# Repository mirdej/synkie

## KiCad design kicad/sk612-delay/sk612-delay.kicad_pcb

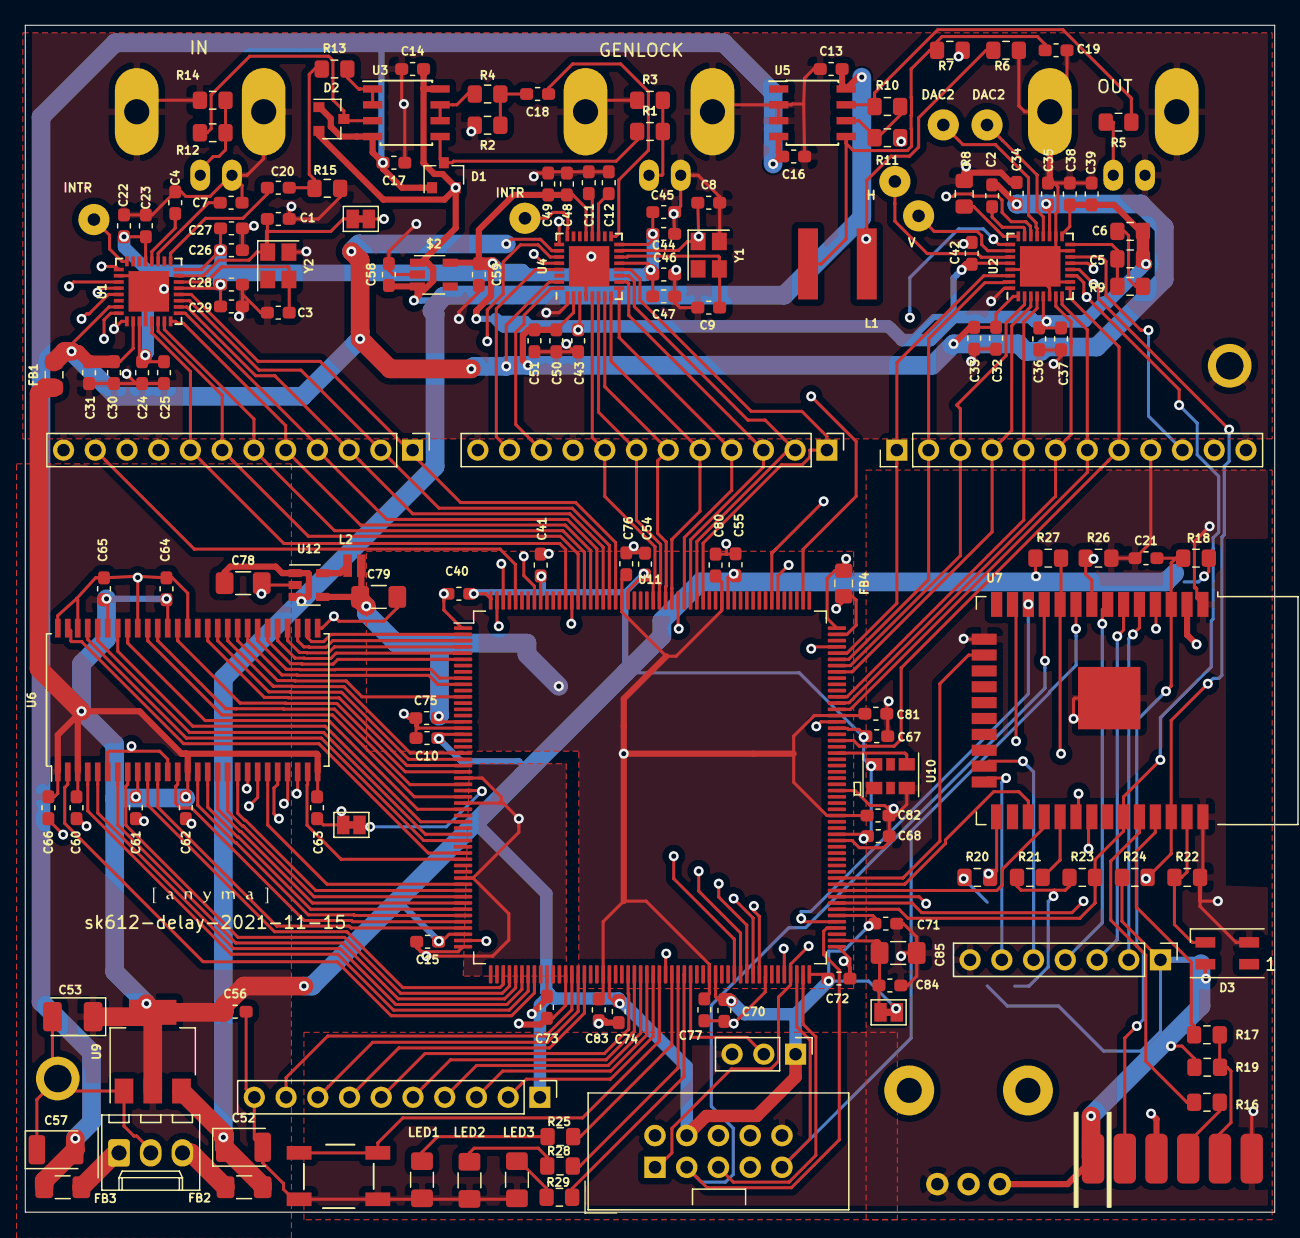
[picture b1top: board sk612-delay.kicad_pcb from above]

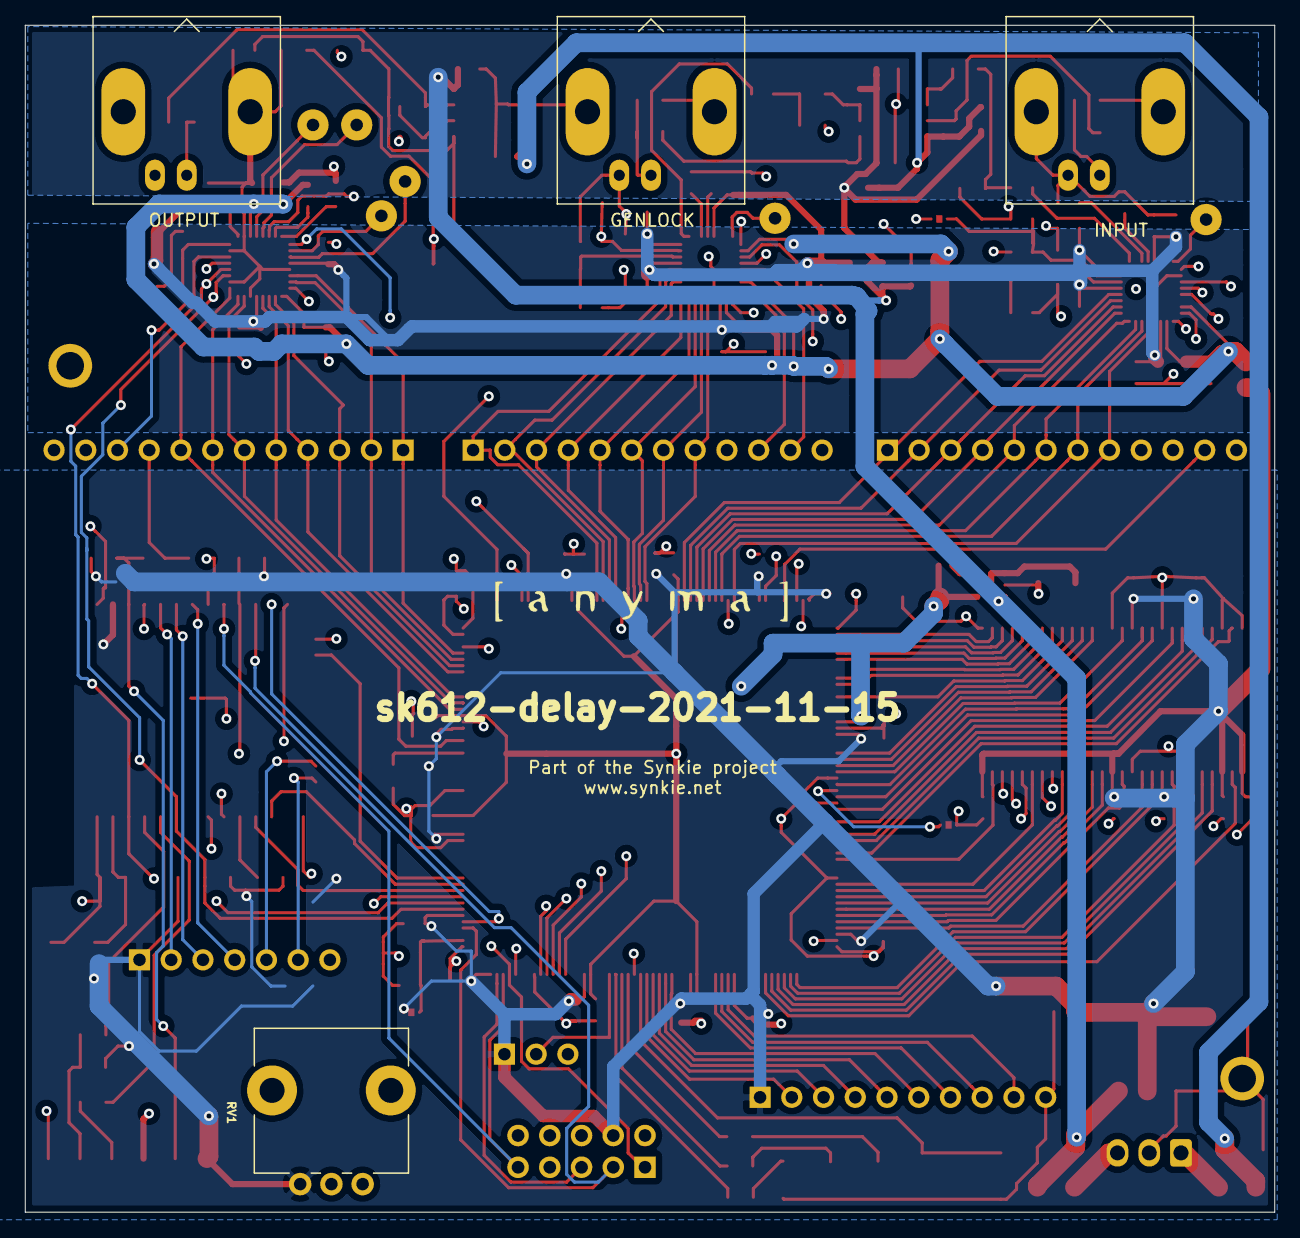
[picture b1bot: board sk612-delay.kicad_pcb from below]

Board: 4 copper layers, 100.0 x 95.0 mm, 166 parts (5 on the bottom side), 159 nets.

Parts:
$2: ADP150; TSOT-23-5
C1, C3, C8, C9: 18p; C_0603_1608Metric_Pad1.05x0.95mm_HandSolder
C2: 2n2; C_0603_1608Metric_Pad1.05x0.95mm_HandSolder
C4, C7, C10, C11, C12, C13, C14, C15, C16, C17, C18, C20, C23, C25, C27, C29, C31, C33, C35, C37, C39, C40, C41, C43, C45, C47, C49, C51, C54, C55, C56, C60, C61, C62, C63, C64, C65, C66, C67, C68, C70, C71, C72, C73, C74, C75, C76, C77, C80, C81, C82, C83, C84: 100n; C_0603_1608Metric_Pad1.05x0.95mm_HandSolder
C5: 12n; C_0805_2012Metric_Pad1.15x1.40mm_HandSolder
C6: 150n; C_0805_2012Metric_Pad1.15x1.40mm_HandSolder
C19: 22p; C_0603_1608Metric_Pad1.05x0.95mm_HandSolder
C21, C58, C59: 1u; C_0603_1608Metric_Pad1.05x0.95mm_HandSolder
C22, C24, C26, C28, C30, C32, C34, C36, C38, C42, C44, C46, C48, C50: 10n; C_0603_1608Metric_Pad1.05x0.95mm_HandSolder
C52, C57: 10u; CP_EIA-3528-21_Kemet-B
C53: 10u; CP_EIA-3528-21_Kemet-B_Pad1.50x2.35mm_HandSolder
C78: 10u; C_1206_3216Metric_Pad1.42x1.75mm_HandSolder
C79: 22u; C_1206_3216Metric_Pad1.42x1.75mm_HandSolder
C85: 33u; C_1206_3216Metric_Pad1.42x1.75mm_HandSolder
D1, D2: BAT54S; SOT-23
D3: SK6812MINI; LED_SK6812MINI_PLCC4_3.5x3.5mm_P1.75mm
D4, D5, D6: LED; C_1206_3216Metric_Pad1.42x1.75mm_HandSolder
FB1, FB4: Ferrite_Bead; L_0805_2012Metric_Pad1.15x1.40mm_HandSolder
FB2, FB3: Ferrite_Bead; L_1206_3216Metric_Pad1.42x1.75mm_HandSolder
H1, H2: MountingHole_Pad; MountingHole_2.2mm_M2_ISO7380_Pad
J1, J23: intr; Solderpad_1mm
J2, J5, J10: Conn_01x12; PinHeader_1x12_P2.54mm_Vertical
J3: vs; Solderpad_1mm
J4: hs; Solderpad_1mm
J6: dac2; Solderpad_1mm
J7: dac3; Solderpad_1mm
J8: Genlock IN; BNC_MOLEX_0731000080_Horizontal
J9: OUT; BNC_MOLEX_0731000080_Horizontal
J11: Conn_01x07; PinHeader_1x07_P2.54mm_Vertical
J12: Conn_01x10; IDC-Header_2x05_P2.54mm_Vertical
J13: Mode-Switch; PinHeader_1x03_P2.54mm_Vertical
J14: Conn_01x10; PinHeader_1x10_P2.54mm_Vertical
J15: Video In; BNC_MOLEX_0731000080_Horizontal
J17: Conn_01x06; Pinhead_SMD_6
J19: Supply; Molex_KK-254_AE-6410-03A_1x03_P2.54mm_Vertical
JP1: Jumper_2_Bridged; SolderJumper-2_P1.3mm_Bridged_Pad1.0x1.5mm
JP2, JP3: Jumper; SolderJumper-2_P1.3mm_Bridged_Pad1.0x1.5mm
L1: 10uH; Murata 1264EY-Inductor
L2: L; L-WUERTH-WE_MAIA
R1, R3, R5, R12, R14: 75; R_0805_2012Metric_Pad1.15x1.40mm_HandSolder
R2, R13: 24; R_0805_2012Metric_Pad1.15x1.40mm_HandSolder
R4, R15: 51; R_0805_2012Metric_Pad1.15x1.40mm_HandSolder
R6, R7: 600; R_0805_2012Metric_Pad1.15x1.40mm_HandSolder
R8: 4k12; R_0805_2012Metric_Pad1.15x1.40mm_HandSolder
R9: 170; R_0805_2012Metric_Pad1.15x1.40mm_HandSolder
R10, R11: 560; R_0805_2012Metric_Pad1.15x1.40mm_HandSolder
R16, R17: 330; R_0805_2012Metric_Pad1.15x1.40mm_HandSolder
R18, R19, R20, R21, R22, R27: 10k; R_0805_2012Metric_Pad1.15x1.40mm_HandSolder
R23, R24: 4k7; R_0805_2012Metric_Pad1.15x1.40mm_HandSolder
R25, R26, R28, R29: 1k; R_0805_2012Metric_Pad1.15x1.40mm_HandSolder
RV1: delay-time; Potentiometer_Alps_RK09L_Single_Vertical
SW1: SW_Push; Alps_Tactile_Switch
U1, U4: ADV7280; LFCSP-32-1EP_5x5mm_P0.5mm_EP3.25x3.25mm
U2: ADV7391; LFCSP-32-1EP_5x5mm_P0.5mm_EP3.25x3.25mm
U3, U5: LMH6643; SOIC-8_3.9x4.9mm_P1.27mm
U6: IS42_S16320F; TSOP-II-54_22.2x10.16mm_P0.8mm
U7: ESP32-WROOM; ESP32-WROOM-32
U8: LOGO; logo_anyma_tiny
U9: AZ1117-3.3; SOT-223-3_TabPin2
U10: OSC-RENESAS
U11: A3P125-PQG208; PQFP-208_28x28mm_P0.5mm
U12: VREG-SC189C; SOT-23-5
U13: LOGO; logo_anyma
Y1: Crystal_GND24; Crystal_SMD_Abracon_ABM8G-4Pin_3.2x2.5mm
Y2: Crystal??; Crystal_SMD_Abracon_ABM8G-4Pin_3.2x2.5mm

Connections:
3V3: C10.1, C15.1, C40.1, C41.1, C53.1, C54.1, C55.1, C56.1, C60.1, C61.1, C62.1, C63.1, C64.1, C65.1, C66.1, C67.1, C68.1, C70.1, C71.1, C72.1, C73.1, C74.1, D3.4, FB1.1, J11.1, J12.4, J13.1, J14.1, J17.1, JP2.2, R18.1, R19.1, R20.1, R21.1, R23.1, R24.1, R27.1, RV1.3, U6.1, U6.3, U6.9, U6.14, U6.27, U6.43, U6.49, U7.2, U9.2, U10.6, U11.18, U11.50, U11.62, U11.72, U11.89, U11.104, U11.110, U11.123, U11.140, U11.170, U11.186, U11.200, U11.208
200MHZ: U10.4, U11.136
+1V5: C75.1, C76.1, C77.1, C79.1, C80.1, C81.1, C82.1, C83.1, L2.1, U11.16, U11.71, U11.88, U11.126, U11.142, U11.171, U11.187, U12.4
+1V8: $2.5, C5.1, C6.1, C22.2, C23.2, C24.2, C25.2, C26.2, C27.2, C28.2, C29.2, C36.2, C37.2, C38.2, C39.2, C42.2, C43.2, C44.2, C45.2, C46.2, C47.2, C48.2, C49.2, C59.1, U1.3, U1.13, U1.16, U1.21, U2.5, U2.17, U2.28, U4.3, U4.13, U4.16, U4.21
+3V3: C2.1, C30.2, C31.2, C32.2, C33.2, C34.2, C35.2, C50.2, C51.2, FB1.2, U1.2, U1.31, U2.1, U2.19, U4.2, U4.26, U4.31
+5V: $2.1, $2.3, C13.2, C14.2, C52.1, C58.1, C78.1, D1.2, D2.2, FB2.1, U3.8, U5.8, U9.3, U12.1, U12.3
-5V: C16.2, C17.2, C57.2, D1.1, D2.1, FB3.1, U3.4, U5.4
/controller/cs: R21.2, U7.29
/controller/en: C21.1, J17.2, R18.2, U7.3
/controller/gpio0: J17.3, R20.2, U7.25
/controller/led: D3.3, R22.1, U7.37
/controller/rx: J17.4, R16.2
/controller/tx: J17.5, R17.2, R19.2
/fpga/btn: SW1.2, U11.80
/fpga/led1: R25.1, U11.82
/fpga/led2: R28.1, U11.83
/fpga/led3: R29.1, U11.84
/fpga/switch: J13.2, U11.85
A0: U6.23, U11.94
A1: U6.24, U11.93
A2: U6.25, U11.92
A3: U6.26, U11.38
A4: U6.29, U11.2
A5: U6.30, U11.3
A6: U6.31, U11.4
A7: U6.32, U11.5
A8: U6.33, U11.6
A9: U6.34, U11.9
A10: U6.22, U11.42
A11: U6.35, U11.10
A12: U6.36, U11.12
AD0: J10.1, U1.12, U11.188
AD1: J10.2, U1.11, U11.189
AD2: J10.3, U1.10, U11.190
AD3: J10.4, U1.9, U11.191
AD4: J10.5, U1.8, U11.192
AD5: J10.6, U1.7, U11.193
AD6: J10.7, U1.6, U11.194
AD7: J10.8, U1.5, U11.196
ADC_IN: C20.1, U1.17
ADC_LLC: J10.10, U1.32, U11.206
ADC_RESET: U1.25, U4.25, U7.31
AD_SFL_OUT: J10.11, U1.29, U11.204
BA0: U6.20, U11.95
BA1: U6.21, U11.96
CAS: U6.17, U11.45
CKE: U6.37, U11.21
CS: U6.19, U11.43
DA0: J2.1, U2.30, U11.152
DA1: J2.2, U2.31, U11.151
DA2: J2.3, U2.2, U11.150
DA3: J2.4, U2.3, U11.149
DA4: J2.5, U2.4, U11.145
DA5: J2.6, U2.7, U11.144
DA6: J2.7, U2.8, U11.143
DA7: J2.8, U2.9, U11.138
DAC_CLK: U2.13, U11.163
DAC_OUT: L1.2, R6.1, U2.22
DAC_RESET: J2.10, U2.14, U7.30
DAC_SFL_IN: U2.25, U11.153
DGMH: U6.39, U11.23
DQ0: U6.2, U11.60
DQ1: U6.4, U11.59
DQ2: U6.5, U11.58
DQ3: U6.7, U11.57
DQ4: U6.8, U11.56
DQ5: U6.10, U11.55
DQ6: U6.11, U11.49
DQ7: U6.13, U11.48
DQ8: U6.42, U11.24
DQ9: U6.44, U11.26
DQ10: U6.45, U11.28
DQ11: U6.47, U11.30
DQ12: U6.48, U11.32
DQ13: U6.50, U11.34
DQ14: U6.51, U11.35
DQ15: U6.53, U11.37
DQML: U6.15, U11.47
GENLOCK_ADC_IN: C18.1, U4.17
GL0: J5.1, U4.12, U11.174
GL1: J5.2, U4.11, U11.175
GL2: J5.3, U4.10, U11.176
GL3: J5.4, U4.9, U11.177
GL4: J5.5, U4.8, U11.179
GL5: J5.6, U4.7, U11.180
GL6: J5.7, U4.6, U11.181
GL7: J5.8, U4.5, U11.182
GL_LLC: J5.10, U4.32, U11.201
GL_SFL_OUT: J5.11, U4.29, U11.158
GND: $2.2, C1.2, C3.1, C4.1, C7.1, C8.2, C9.1, C10.2, C11.1, C12.1, C13.1, C14.1, C15.2, C16.1, C17.1, C19.2, C21.2, C22.1, C23.1, C24.1, C25.1, C26.1, C27.1, C28.1, C29.1, C30.1, C31.1, C32.1, C33.1, C34.1, C35.1, C36.1, C37.1, C38.1, C39.1, C40.2, C41.2, C42.1, C43.1, C44.1, C45.1, C46.1, C47.1, C48.1, C49.1, C50.1, C51.1, C52.2, C53.2, C54.2, C55.2, C56.2, C57.1, C58.2, C59.2, C60.2, C61.2, C62.2, C63.2, C64.2, C65.2, C66.2, C67.2, C68.2, C70.2, C71.2, C72.2, C73.2, C74.2, C75.2, C76.2, C77.2, C78.2, C79.2, C80.2, C81.2, C82.2, C83.2, C84.2, C85.2, D3.2, D4.1, D5.1, D6.1, FB4.1, H1.1, H2.1, J2.9, J2.12, J5.9, J5.12, J8.2, J9.2, J10.9, J10.12, J11.7, J12.2, J12.10, J13.3, J14.10, J15.2, J17.6, J19.2, JP3.1, R3.1, R4.1, R6.2, R7.2, R8.2, R11.2, R14.1, R15.1, R22.2, R26.2, RV1.1, SW1.1, U1.1, U1.4, U1.26, U1.33, U2.6, U2.10, U2.15, U2.18, U2.29, U2.32, U2.33, U4.1, U4.4, U4.33, U5.2, U5.3, U6.6, U6.12, U6.28, U6.41, U6.46, U6.52, U6.54, U7.1, U7.15, U7.38, U7.39, U9.1, U10.3, U11.1, U11.17, U11.25, U11.29, U11.41, U11.52, U11.65, U11.81, U11.97, U11.105, U11.122, U11.130, U11.141, U11.156, U11.162, U11.178, U11.195, U12.2, Y1.4, Y2.4
GNDS: FB4.2, U11.51, U11.100, U11.155, U11.207
MISO: U7.16, U11.116
MOSI: U7.28, U11.114
unnamed: C1.1, JP1.2, U1.15, Y2.1
unnamed: C2.2, U2.23
unnamed: C3.2, U1.14, Y2.3
unnamed: C4.2, U1.20
unnamed: C5.2, R9.2, U2.16
unnamed: C6.2, R9.1
unnamed: C7.2, U1.19
unnamed: C8.1, JP1.1, U4.15, Y1.1
unnamed: C9.2, U4.14, Y1.3
unnamed: C11.2, U4.20
unnamed: C12.2, U4.19
unnamed: C18.2, R2.1, R4.2
unnamed: C19.1, L1.1, R7.1, U5.5
unnamed: C20.2, R13.1, R15.2
unnamed: C84.1, C85.1, JP2.1, U11.106
unnamed: D1.3, R1.1, U3.5
unnamed: D2.3, R12.1, U3.3
unnamed: D4.2, R25.2
unnamed: D5.2, R28.2
unnamed: D6.2, R29.2
unnamed: FB2.2, J19.3
unnamed: FB3.2, J19.1
unnamed: J1.1, U4.24
unnamed: J3.1, U2.26
unnamed: J4.1, U2.27
unnamed: J6.1, U2.21
unnamed: J7.1, U2.20
unnamed: J8.1, R1.2, R3.2
unnamed: J9.1, R5.2
unnamed: J11.2, U7.5
unnamed: J11.3, U7.6
unnamed: J11.4, U7.7
unnamed: J11.5, U7.23
unnamed: J11.6, U7.24
unnamed: J14.2, U11.79
unnamed: J14.3, U11.78
unnamed: J14.4, U11.77
unnamed: J14.5, U11.76
unnamed: J14.6, U11.75
unnamed: J14.7, U11.68
unnamed: J14.8, U11.67
unnamed: J14.9, U11.66
unnamed: J15.1, R12.2, R14.2
unnamed: J23.1, U1.24
unnamed: JP3.2, U11.27
unnamed: L2.2, U12.5
unnamed: R2.2, U3.6, U3.7
unnamed: R8.1, U2.24
unnamed: R10.1, R11.1, U5.6
unnamed: R5.1, R10.2, U5.7
unnamed: R13.2, U3.1, U3.2
unnamed: R16.1, U7.34
unnamed: R17.1, U7.35
unnamed: RV1.2, U7.4
RAM_CLK: U6.38, U11.22
RAS: U6.18, U11.44
SCK: U7.27, U11.115
SCL: R24.2, U1.28, U2.12, U4.28, U7.36, U11.112
SDA: R23.2, U1.27, U2.11, U4.27, U7.33, U11.111
SSEL: U7.13, U11.113
TCK: J12.1, R26.1, U7.8, U11.101
TDI: J12.9, U7.9, U11.102
TDO: J12.3, U7.11, U11.108
TMS: J12.5, R27.2, U7.10, U11.103
TRST: U7.12, U11.109
WE: U6.16, U11.46

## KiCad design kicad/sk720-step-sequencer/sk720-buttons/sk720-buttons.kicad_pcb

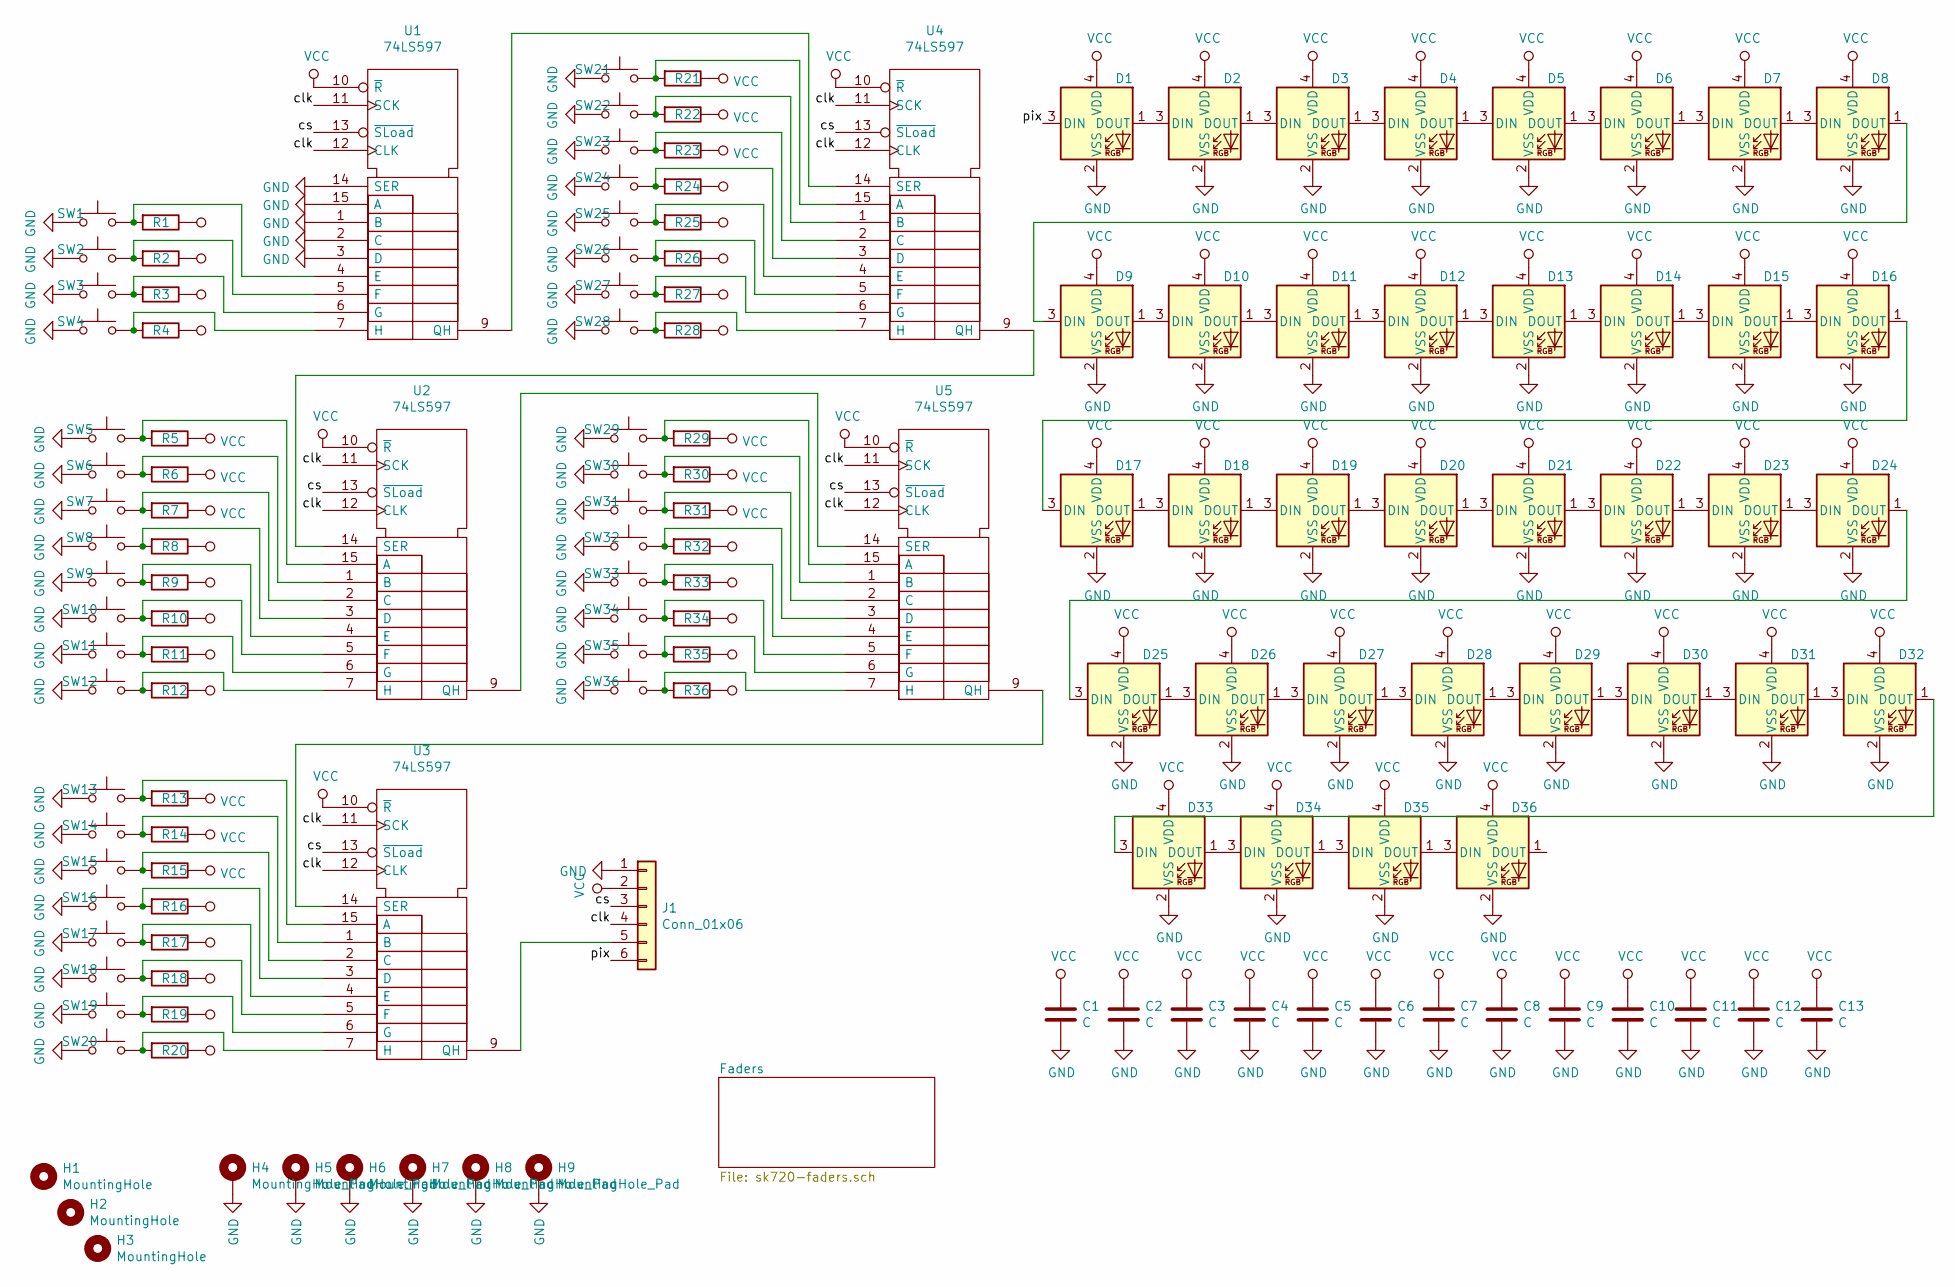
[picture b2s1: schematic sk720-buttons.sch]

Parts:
C1, C2, C3, C4, C5, C6, C7, C8, C9, C10, C11, C12, C13: C; C_0603_1608Metric_Pad1.05x0.95mm_HandSolder
D1, D2, D3, D4, D5, D6, D7, D8, D9, D10, D11, D12, D13, D14, D15, D16, D17, D18, D19, D20, D21, D22, D23, D24, D25, D26, D27, D28, D29, D30, D31, D32, D33, D34, D35, D36: SK6812MINI; LED_SK6812MINI_PLCC4_3.5x3.5mm_P1.75mm
H1, H2, H3: MountingHole; MountingHole_3mm
H4, H5, H6, H7, H8, H9: MountingHole_Pad; MountingHole_3.2mm_M3_DIN965_Pad
J1: Conn_01x06; PinHeader_1x06_P2.54mm_Vertical
R1, R2, R3, R4, R5, R6, R7, R8, R9, R10, R11, R12, R13, R14, R15, R16, R17, R18, R19, R20, R21, R22, R23, R24, R25, R26, R27, R28, R29, R30, R31, R32, R33, R34, R35, R36: R; R_0805_2012Metric_Pad1.15x1.40mm_HandSolder
SW1, SW2, SW3, SW4, SW5, SW6, SW7, SW8, SW9, SW10, SW11, SW12, SW13, SW14, SW15, SW16, SW17, SW18, SW19, SW20, SW21, SW22, SW23, SW24, SW25, SW26, SW27, SW28, SW29, SW30, SW31, SW32, SW33, SW34, SW35, SW36: SW_Push; Alps_Tactile_Switch
U1, U2, U3, U4, U5: 74LS597; SOP-16_4.4x10.4mm_P1.27mm

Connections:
/clk: J1.4, U1.11 (SCK), U1.12 (CLK), U2.11 (SCK), U2.12 (CLK), U3.11 (SCK), U3.12 (CLK), U4.11 (SCK), U4.12 (CLK), U5.11 (SCK), U5.12 (CLK)
/cs: J1.3, U1.13 (~SLoad), U2.13 (~SLoad), U3.13 (~SLoad), U4.13 (~SLoad), U5.13 (~SLoad)
/pix: D1.3 (DIN), J1.6
GND: C1.2, C2.2, C3.2, C4.2, C5.2, C6.2, C7.2, C8.2, C9.2, C10.2, C11.2, C12.2, C13.2, D1.2 (VSS), D2.2 (VSS), D3.2 (VSS), D4.2 (VSS), D5.2 (VSS), D6.2 (VSS), D7.2 (VSS), D8.2 (VSS), D9.2 (VSS), D10.2 (VSS), D11.2 (VSS), D12.2 (VSS), D13.2 (VSS), D14.2 (VSS), D15.2 (VSS), D16.2 (VSS), D17.2 (VSS), D18.2 (VSS), D19.2 (VSS), D20.2 (VSS), D21.2 (VSS), D22.2 (VSS), D23.2 (VSS), D24.2 (VSS), D25.2 (VSS), D26.2 (VSS), D27.2 (VSS), D28.2 (VSS), D29.2 (VSS), D30.2 (VSS), D31.2 (VSS), D32.2 (VSS), D33.2 (VSS), D34.2 (VSS), D35.2 (VSS), D36.2 (VSS), H4.1, H5.1, H6.1, H7.1, H8.1, H9.1, J1.1, SW1.1, SW2.1, SW3.1, SW4.1, SW5.1, SW6.1, SW7.1, SW8.1, SW9.1, SW10.1, SW11.1, SW12.1, SW13.1, SW14.1, SW15.1, SW16.1, SW17.1, SW18.1, SW19.1, SW20.1, SW21.1, SW22.1, SW23.1, SW24.1, SW25.1, SW26.1, SW27.1, SW28.1, SW29.1, SW30.1, SW31.1, SW32.1, SW33.1, SW34.1, SW35.1, SW36.1, U1.1 (B), U1.2 (C), U1.3 (D), U1.8 (GND), U1.14 (SER), U1.15 (A), U2.8 (GND), U3.8 (GND), U4.8 (GND), U5.8 (GND); also elsewhere on the board
unnamed: D1.1 (DOUT), D2.3 (DIN)
unnamed: D2.1 (DOUT), D3.3 (DIN)
unnamed: D3.1 (DOUT), D4.3 (DIN)
unnamed: D4.1 (DOUT), D5.3 (DIN)
unnamed: D5.1 (DOUT), D6.3 (DIN)
unnamed: D6.1 (DOUT), D7.3 (DIN)
unnamed: D7.1 (DOUT), D8.3 (DIN)
unnamed: D8.1 (DOUT), D9.3 (DIN)
unnamed: D10.1 (DOUT), D11.3 (DIN)
unnamed: D9.1 (DOUT), D10.3 (DIN)
unnamed: D11.1 (DOUT), D12.3 (DIN)
unnamed: D12.1 (DOUT), D13.3 (DIN)
unnamed: D13.1 (DOUT), D14.3 (DIN)
unnamed: D14.1 (DOUT), D15.3 (DIN)
unnamed: D15.1 (DOUT), D16.3 (DIN)
unnamed: D16.1 (DOUT), D17.3 (DIN)
unnamed: D17.1 (DOUT), D18.3 (DIN)
unnamed: D18.1 (DOUT), D19.3 (DIN)
unnamed: D19.1 (DOUT), D20.3 (DIN)
unnamed: D20.1 (DOUT), D21.3 (DIN)
unnamed: D21.1 (DOUT), D22.3 (DIN)
unnamed: D22.1 (DOUT), D23.3 (DIN)
unnamed: D23.1 (DOUT), D24.3 (DIN)
unnamed: D24.1 (DOUT), D25.3 (DIN)
unnamed: D25.1 (DOUT), D26.3 (DIN)
unnamed: D26.1 (DOUT), D27.3 (DIN)
unnamed: D27.1 (DOUT), D28.3 (DIN)
unnamed: D28.1 (DOUT), D29.3 (DIN)
unnamed: D29.1 (DOUT), D30.3 (DIN)
unnamed: D30.1 (DOUT), D31.3 (DIN)
unnamed: D31.1 (DOUT), D32.3 (DIN)
unnamed: D32.1 (DOUT), D33.3 (DIN)
unnamed: D33.1 (DOUT), D34.3 (DIN)
unnamed: D34.1 (DOUT), D35.3 (DIN)
unnamed: D35.1 (DOUT), D36.3 (DIN)
unnamed: J1.5, U3.9 (QH)
unnamed: R1.2, SW1.2, U1.4 (E)
unnamed: R2.2, SW2.2, U1.5 (F)
unnamed: R3.2, SW3.2, U1.6 (G)
unnamed: R4.2, SW4.2, U1.7 (H)
unnamed: R5.2, SW5.2, U2.15 (A)
unnamed: R6.2, SW6.2, U2.1 (B)
unnamed: R7.2, SW7.2, U2.2 (C)
unnamed: R8.2, SW8.2, U2.3 (D)
unnamed: R9.2, SW9.2, U2.4 (E)
unnamed: R10.2, SW10.2, U2.5 (F)
unnamed: R11.2, SW11.2, U2.6 (G)
unnamed: R12.2, SW12.2, U2.7 (H)
unnamed: R13.2, SW13.2, U3.15 (A)
unnamed: R14.2, SW14.2, U3.1 (B)
unnamed: R15.2, SW15.2, U3.2 (C)
unnamed: R16.2, SW16.2, U3.3 (D)
unnamed: R17.2, SW17.2, U3.4 (E)
unnamed: R18.2, SW18.2, U3.5 (F)
unnamed: R19.2, SW19.2, U3.6 (G)
unnamed: R20.2, SW20.2, U3.7 (H)
unnamed: R21.2, SW21.2, U4.15 (A)
unnamed: R22.2, SW22.2, U4.1 (B)
unnamed: R23.2, SW23.2, U4.2 (C)
unnamed: R24.2, SW24.2, U4.3 (D)
unnamed: R25.2, SW25.2, U4.4 (E)
unnamed: R26.2, SW26.2, U4.5 (F)
unnamed: R27.2, SW27.2, U4.6 (G)
unnamed: R28.2, SW28.2, U4.7 (H)
unnamed: R29.2, SW29.2, U5.15 (A)
unnamed: R30.2, SW30.2, U5.1 (B)
unnamed: R31.2, SW31.2, U5.2 (C)
unnamed: R32.2, SW32.2, U5.3 (D)
unnamed: R33.2, SW33.2, U5.4 (E)
unnamed: R34.2, SW34.2, U5.5 (F)
unnamed: R35.2, SW35.2, U5.6 (G)
unnamed: R36.2, SW36.2, U5.7 (H)
unnamed: U1.9 (QH), U4.14 (SER)
unnamed: U2.9 (QH), U5.14 (SER)
unnamed: U2.14 (SER), U4.9 (QH)
unnamed: U3.14 (SER), U5.9 (QH)
VCC: C1.1, C2.1, C3.1, C4.1, C5.1, C6.1, C7.1, C8.1, C9.1, C10.1, C11.1, C12.1, C13.1, D1.4 (VDD), D2.4 (VDD), D3.4 (VDD), D4.4 (VDD), D5.4 (VDD), D6.4 (VDD), D7.4 (VDD), D8.4 (VDD), D9.4 (VDD), D10.4 (VDD), D11.4 (VDD), D12.4 (VDD), D13.4 (VDD), D14.4 (VDD), D15.4 (VDD), D16.4 (VDD), D17.4 (VDD), D18.4 (VDD), D19.4 (VDD), D20.4 (VDD), D21.4 (VDD), D22.4 (VDD), D23.4 (VDD), D24.4 (VDD), D25.4 (VDD), D26.4 (VDD), D27.4 (VDD), D28.4 (VDD), D29.4 (VDD), D30.4 (VDD), D31.4 (VDD), D32.4 (VDD), D33.4 (VDD), D34.4 (VDD), D35.4 (VDD), D36.4 (VDD), J1.2, R1.1, R2.1, R3.1, R4.1, R5.1, R6.1, R7.1, R8.1, R9.1, R10.1, R11.1, R12.1, R13.1, R14.1, R15.1, R16.1, R17.1, R18.1, R19.1, R20.1, R21.1, R22.1, R23.1, R24.1, R25.1, R26.1, R27.1, R28.1, R29.1, R30.1, R31.1, R32.1, R33.1, R34.1, R35.1, R36.1, U1.10 (~R), U1.16 (VCC), U2.10 (~R), U2.16 (VCC), U3.10 (~R), U3.16 (VCC), U4.10 (~R), U4.16 (VCC), U5.10 (~R), U5.16 (VCC); also elsewhere on the board

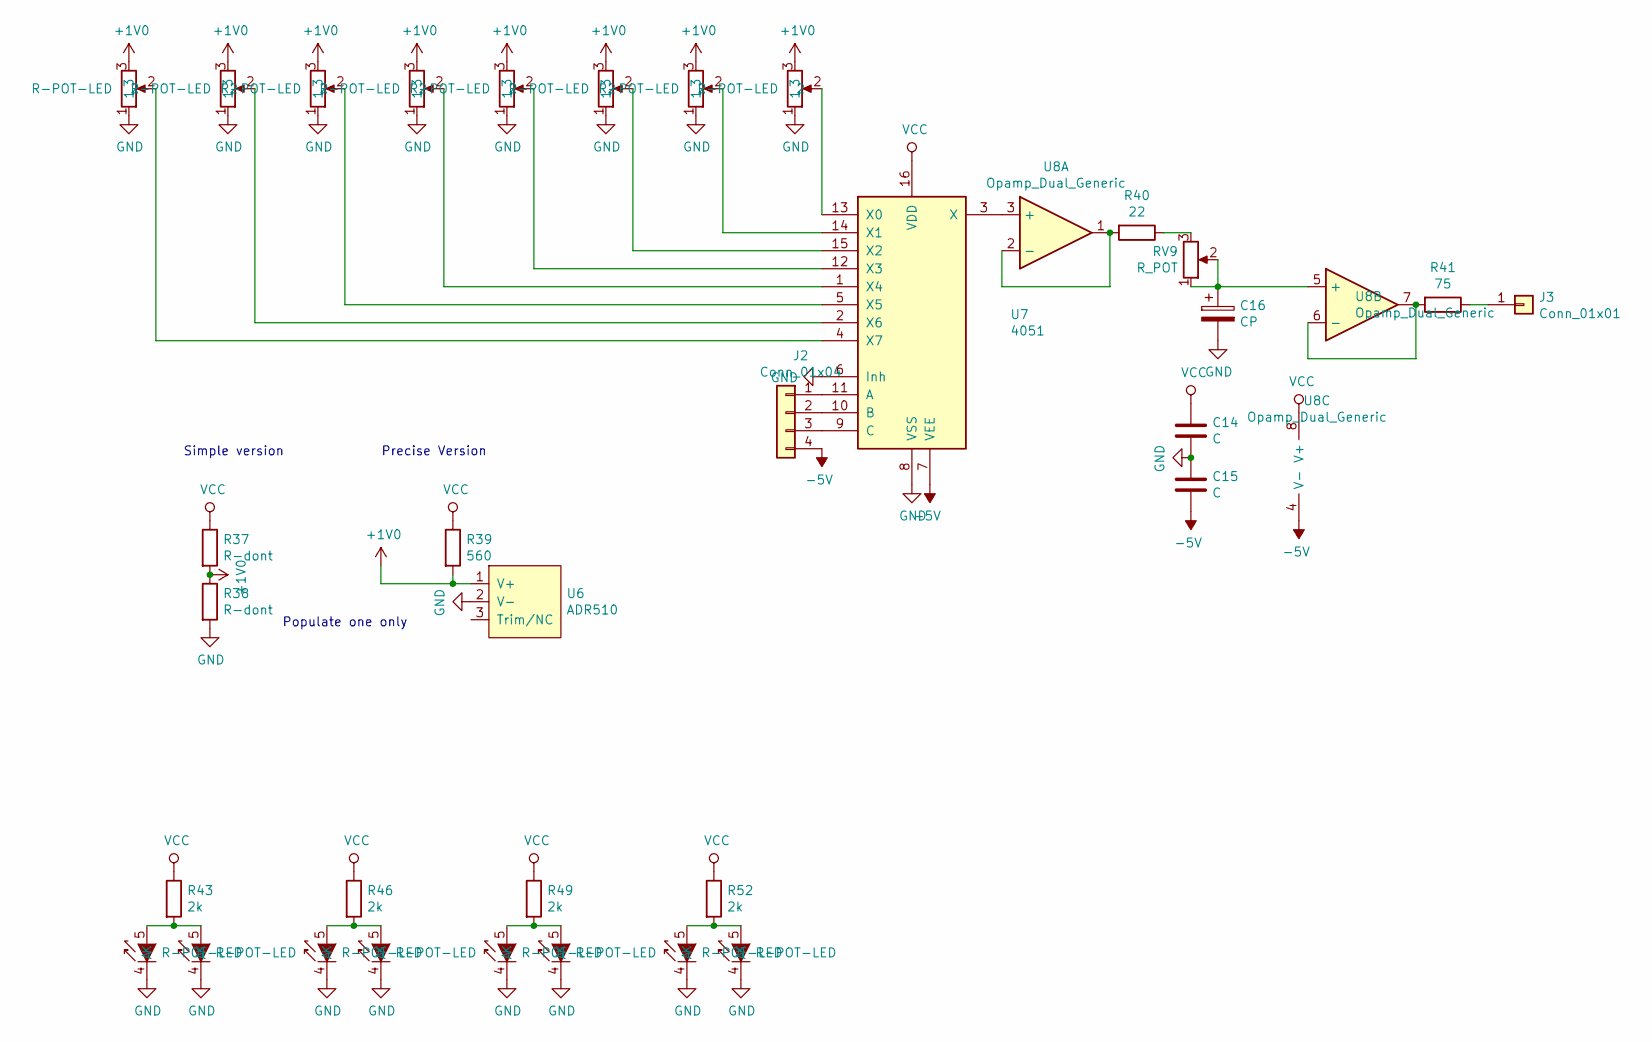
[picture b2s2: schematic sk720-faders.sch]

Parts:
C14, C15: C; C_0603_1608Metric_Pad1.05x0.95mm_HandSolder
C16: CP; CP_EIA-3528-21_Kemet-B_Pad1.50x2.35mm_HandSolder
J2: Conn_01x04; PinHeader_1x04_P2.54mm_Vertical
J3: Conn_01x01; Solderpad_1mm
R37, R38: R-dont; C_0805_2012Metric_Pad1.15x1.40mm_HandSolder
R39: 560; C_0805_2012Metric_Pad1.15x1.40mm_HandSolder
R40: 22; C_0805_2012Metric_Pad1.15x1.40mm_HandSolder
R41: 75; C_0805_2012Metric_Pad1.15x1.40mm_HandSolder
R42, R44, R45, R47, R48, R50, R51, R53: R-POT-LED; PTL20
R43, R46, R49, R52: 2k; R_0805_2012Metric_Pad1.15x1.40mm_HandSolder
RV9: R_POT; Potentiometer_Alps_RK09K_Single_Vertical
U6: ADR510; SOT-23
U7: 4051; SOIC-16_3.9x9.9mm_P1.27mm
U8: Opamp_Dual_Generic; SOIC-8_3.9x4.9mm_P1.27mm

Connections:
+1V0: R37.2, R38.1, R39.2, R42.3, R44.3, R45.3, R47.3, R48.3, R50.3, R51.3, R53.3, U6.1 (V+)
-5V: C15.2, J2.4, U7.7 (VEE), U8.4 (V-)
GND: C14.2, C15.1, C16.2, R38.2, R42.1, R42.4 (K), R44.1, R44.4 (K), R45.1, R45.4 (K), R47.1, R47.4 (K), R48.1, R48.4 (K), R50.1, R50.4 (K), R51.1, R51.4 (K), R53.1, R53.4 (K), U6.2 (V-), U7.6 (Inh), U7.8 (VSS); also elsewhere on the board
unnamed: C16.1, RV9.1, RV9.2, U8.5 (+)
unnamed: J2.1, U7.11 (A)
unnamed: J2.2, U7.10 (B)
unnamed: J2.3, U7.9 (C)
unnamed: J3.1, R41.1
unnamed: R40.1, RV9.3
unnamed: R40.2, U8.1, U8.2 (-)
unnamed: R41.2, U8.6 (-), U8.7
unnamed: R42.2, U7.4 (X7)
unnamed: R42.5 (A), R43.2, R44.5 (A)
unnamed: R44.2, U7.2 (X6)
unnamed: R45.2, U7.5 (X5)
unnamed: R45.5 (A), R46.2, R47.5 (A)
unnamed: R47.2, U7.1 (X4)
unnamed: R48.2, U7.12 (X3)
unnamed: R48.5 (A), R49.2, R50.5 (A)
unnamed: R50.2, U7.15 (X2)
unnamed: R51.2, U7.14 (X1)
unnamed: R51.5 (A), R52.2, R53.5 (A)
unnamed: R53.2, U7.13 (X0)
unnamed: U7.3 (X), U8.3 (+)
VCC: C14.1, R37.1, R39.1, R43.1, R46.1, R49.1, R52.1, U7.16 (VDD), U8.8 (V+); also elsewhere on the board

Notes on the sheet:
Simple version
Precise Version
Populate one only

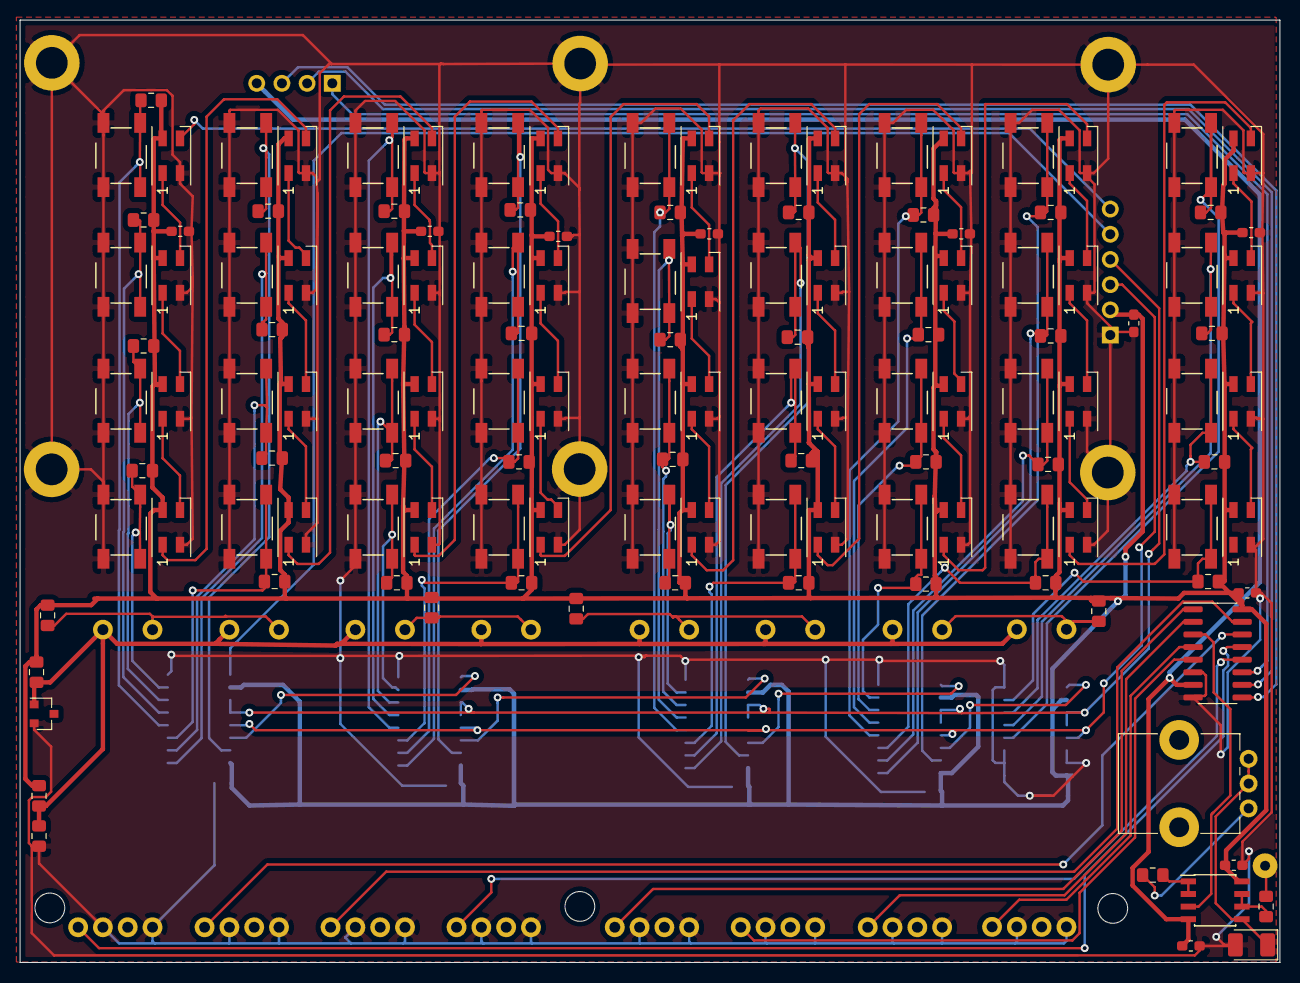
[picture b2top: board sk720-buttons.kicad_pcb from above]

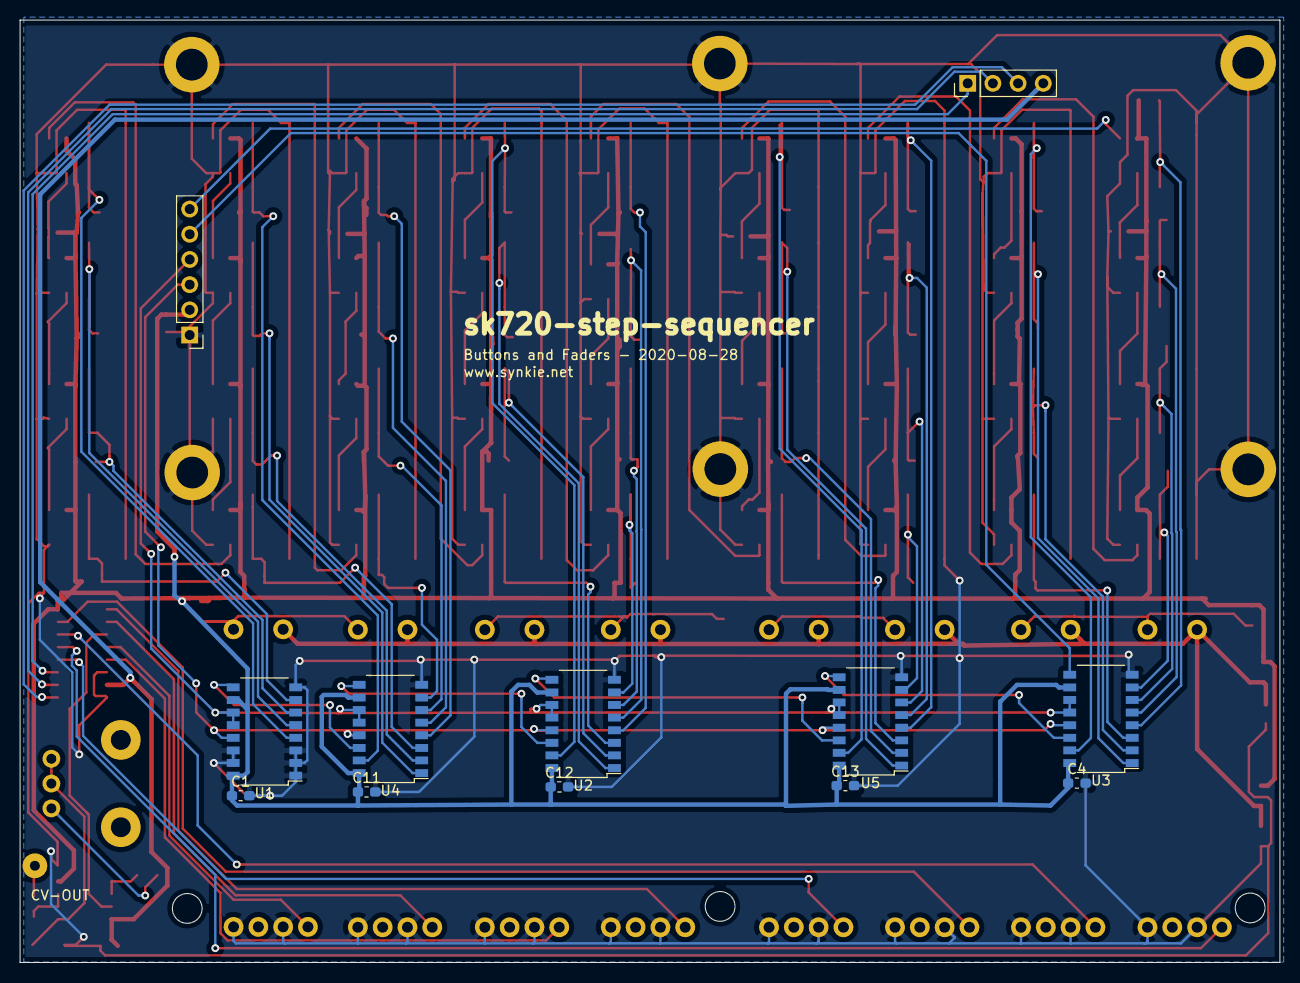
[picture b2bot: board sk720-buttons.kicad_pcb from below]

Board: 2 copper layers, 127.0 x 95.0 mm, 162 parts (12 on the bottom side), 104 nets.

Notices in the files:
parts and their libraries:
Copyright 2016 Accelerated Designs. All rights reserved.
